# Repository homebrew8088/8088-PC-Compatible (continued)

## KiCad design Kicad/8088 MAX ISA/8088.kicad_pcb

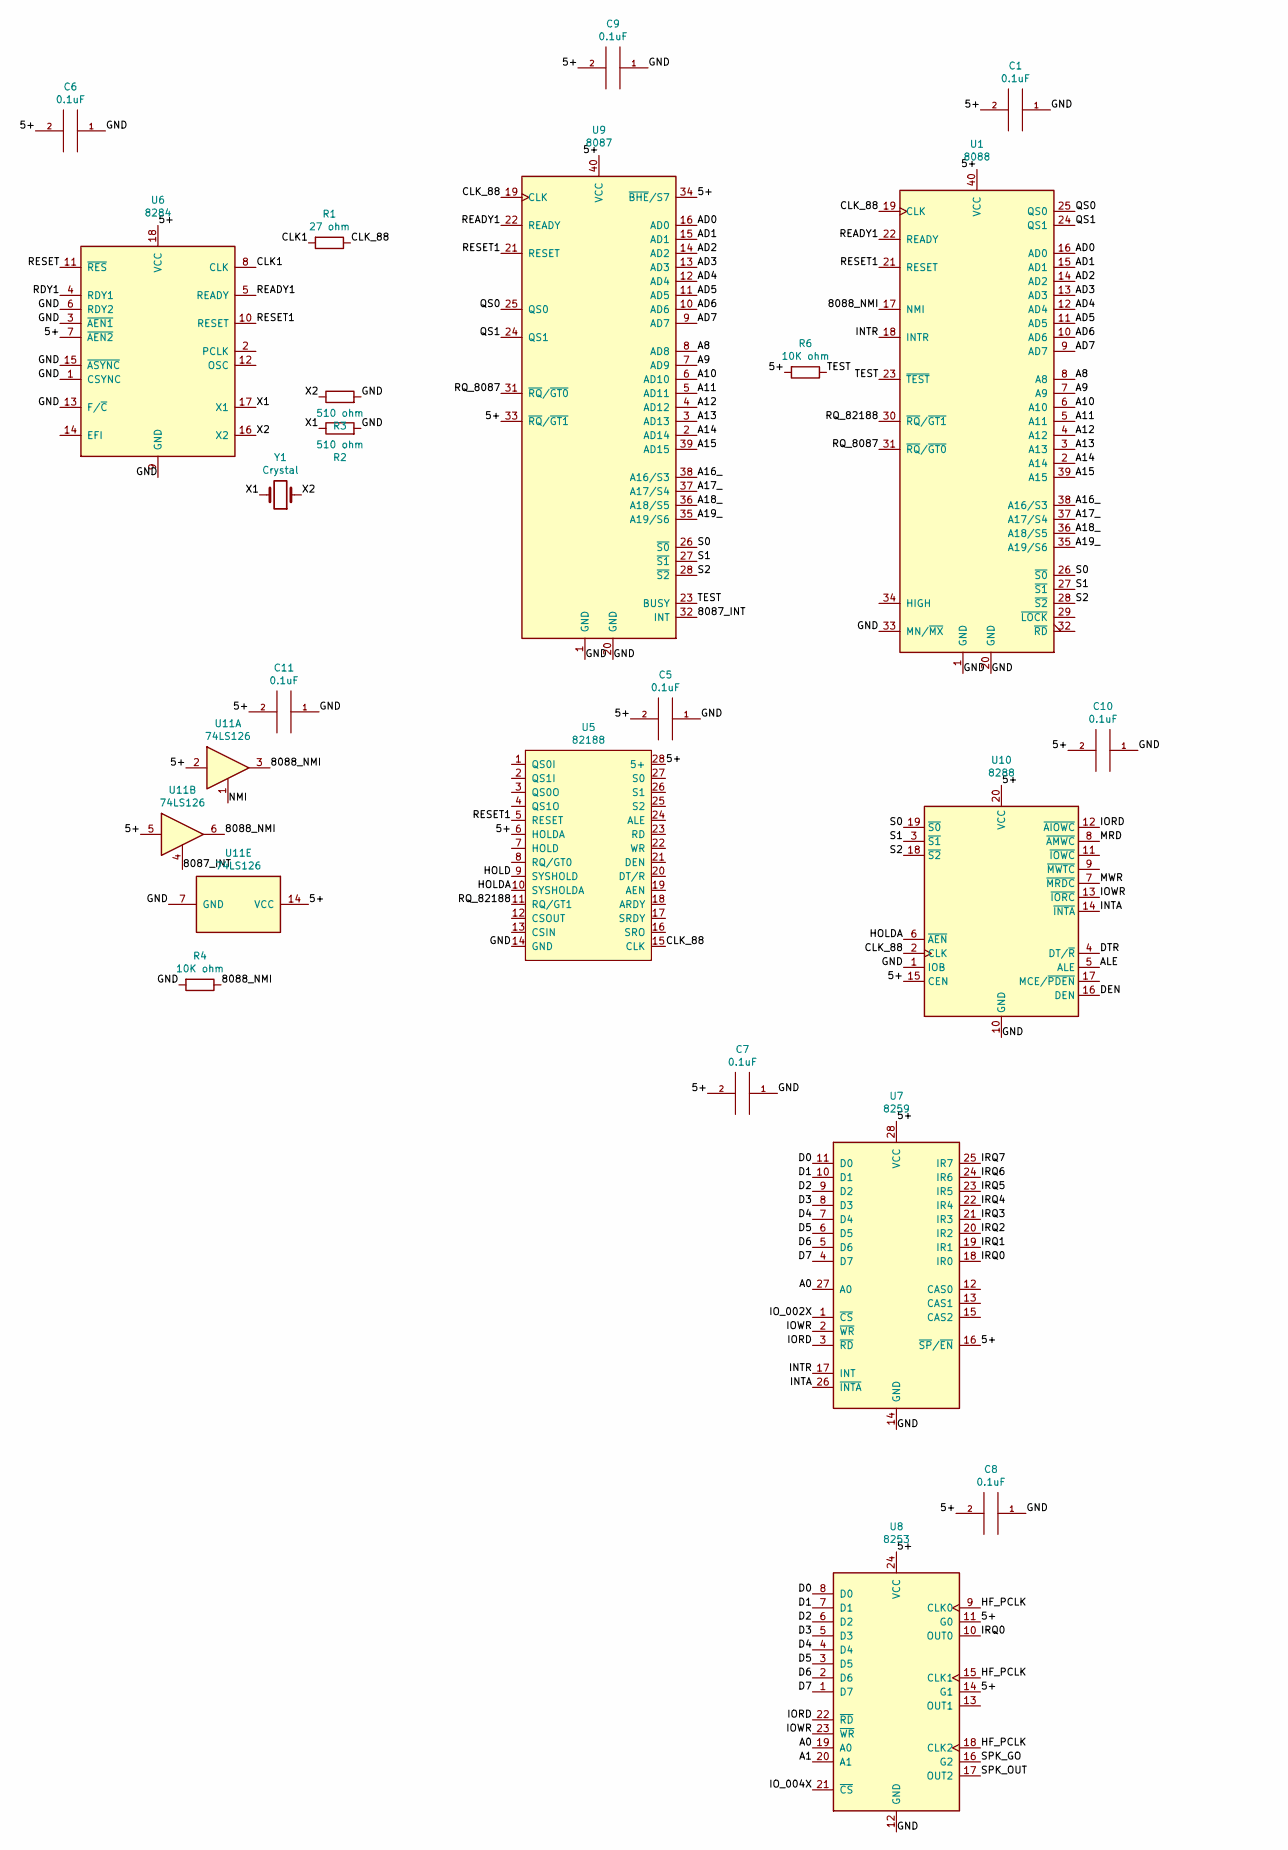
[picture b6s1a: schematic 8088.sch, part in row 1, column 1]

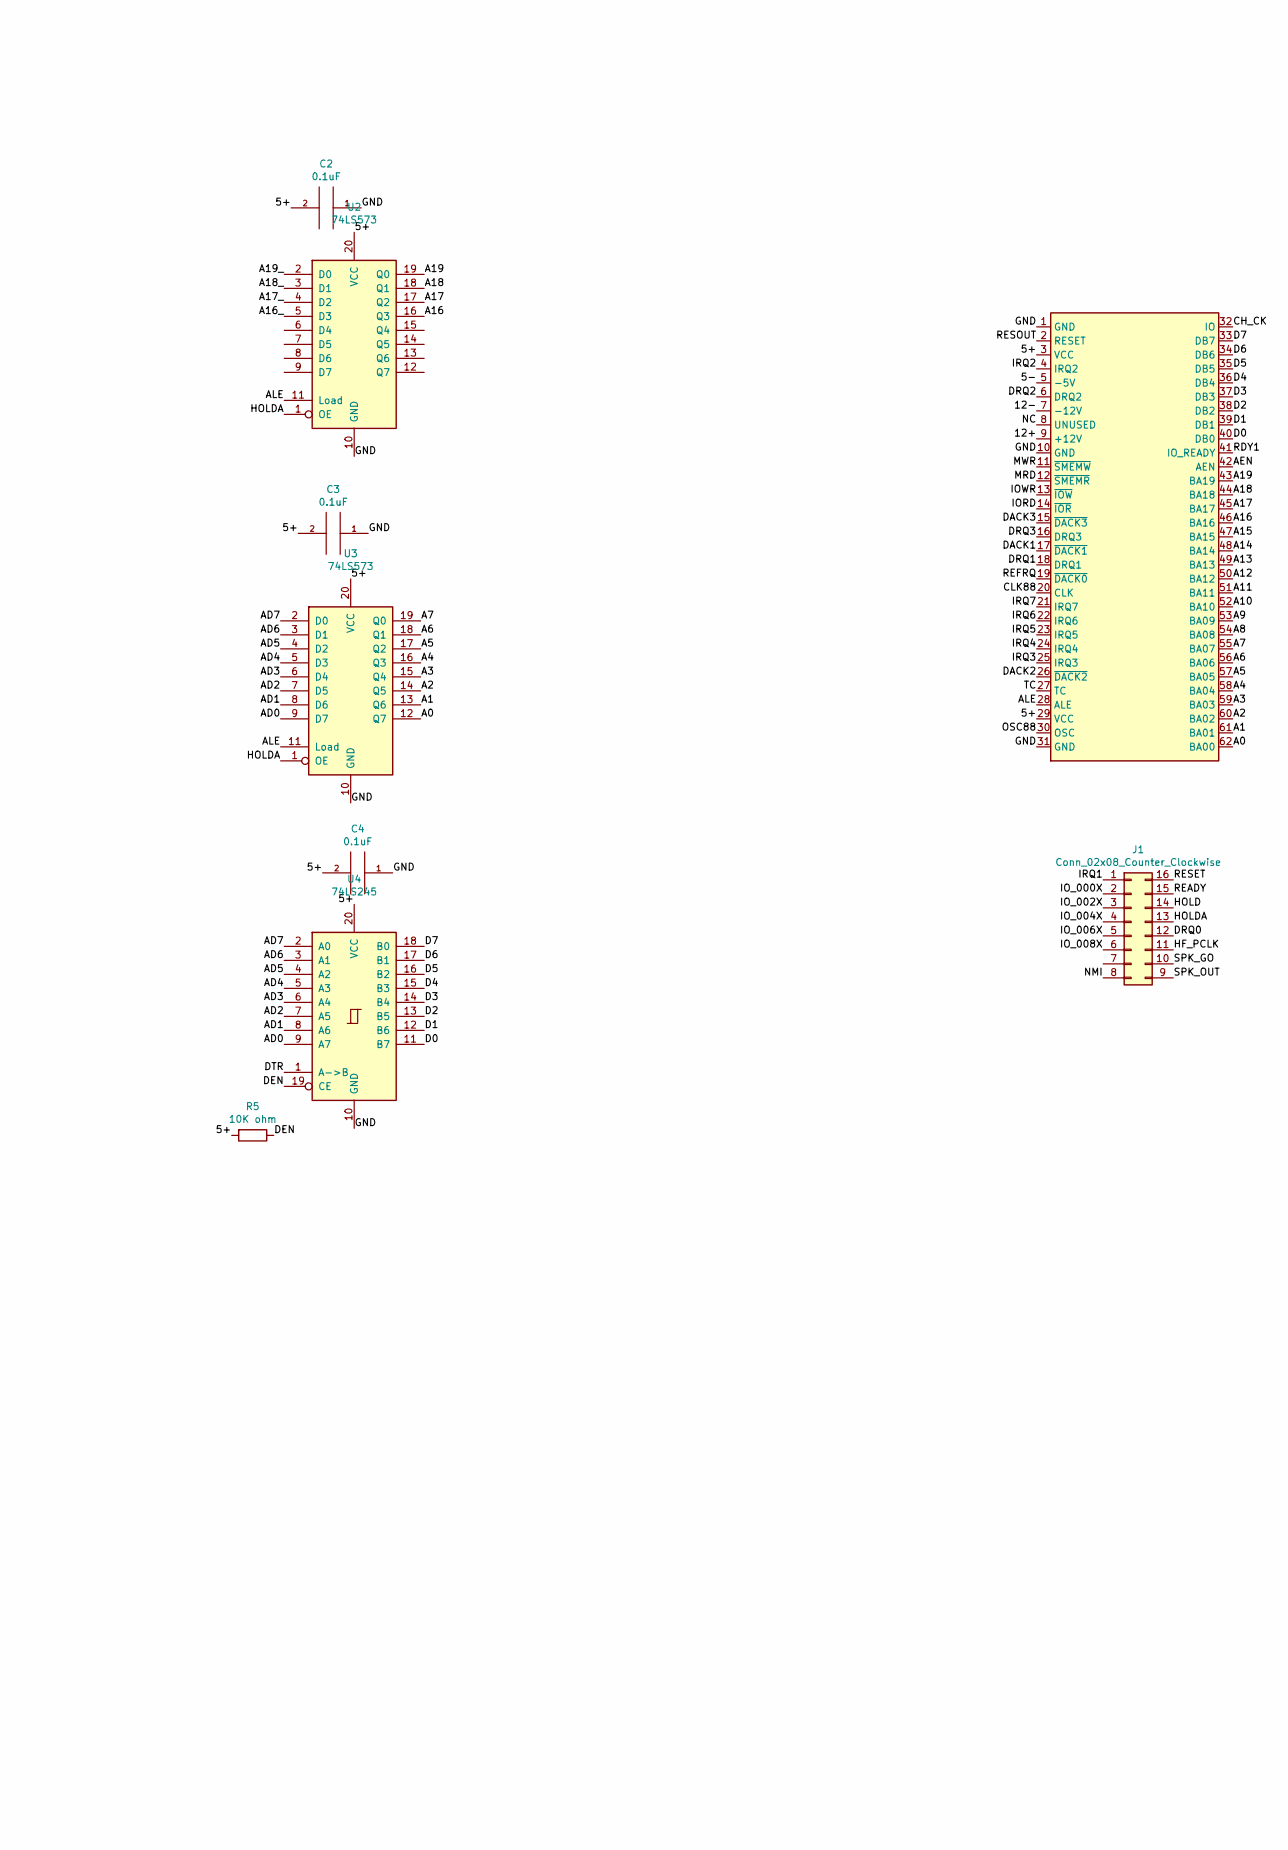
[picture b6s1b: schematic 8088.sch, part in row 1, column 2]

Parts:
C1, C2, C3, C4, C5, C6, C7, C8, C9, C10, C11: 0.1uF; C_Disc_D4.3mm_W1.9mm_P5.00mm
J1: Conn_02x08_Counter_Clockwise; 16_EDGE_CARD_BUS
J9: Bus_ISA_8bit; BUS_8_BIT
R1: 27 ohm; R_Axial_DIN0207_L6.3mm_D2.5mm_P10.16mm_Horizontal
R2, R3: 510 ohm; R_Axial_DIN0207_L6.3mm_D2.5mm_P10.16mm_Horizontal
R4, R5, R6: 10K ohm; R_Axial_DIN0207_L6.3mm_D2.5mm_P10.16mm_Horizontal
U1: 8088; DIP-40_W15.24mm
U2, U3: 74LS573; DIP-20_W7.62mm
U4: 74LS245; DIP-20_W7.62mm
U5: 82188; DIP-28_W15.24mm
U6: 8284; DIP-18_W7.62mm
U7: 8259; DIP-28_W15.24mm
U8: 8253; DIP-24_W15.24mm
U9: 8087; DIP-40_W15.24mm
U10: 8288; DIP-20_W7.62mm
U11: 74LS126; DIP-14_W7.62mm
Y1: Crystal; Crystal_HC18-U_Vertical

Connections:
/5+: C1.2, C2.2, C3.2, C4.2, C5.2, C6.2, C7.2, C8.2, C9.2, C10.2, C11.2, J9.3 (VCC), J9.29 (VCC), R5.2, R6.2, U1.40 (VCC), U2.20 (VCC), U3.20 (VCC), U4.20 (VCC), U5.6 (HOLDA), U5.28 (5+), U6.7 (~AEN2~), U6.18 (VCC), U7.16 (~SP~/~EN~), U7.28 (VCC), U8.11 (G0), U8.14 (G1), U8.24 (VCC), U9.33 (~RQ~/~GT1~), U9.34 (~BHE~/S7), U9.40 (VCC), U10.15 (CEN), U10.20 (VCC), U11.2, U11.5, U11.14 (VCC)
/5-: J9.5 (-5V)
/12+: J9.9 (+12V)
/12-: J9.7 (-12V)
/8087_INT: U9.32 (INT), U11.4
/8088_NMI: R4.1, U1.17 (NMI), U11.3, U11.6
/A0: J9.62 (BA00), U3.12 (Q7), U7.27 (A0), U8.19 (A0)
/A1: J9.61 (BA01), U3.13 (Q6), U8.20 (A1)
/A2: J9.60 (BA02), U3.14 (Q5)
/A3: J9.59 (BA03), U3.15 (Q4)
/A4: J9.58 (BA04), U3.16 (Q3)
/A5: J9.57 (BA05), U3.17 (Q2)
/A6: J9.56 (BA06), U3.18 (Q1)
/A7: J9.55 (BA07), U3.19 (Q0)
/A8: J9.54 (BA08), U1.8 (A8), U9.8 (AD8)
/A9: J9.53 (BA09), U1.7 (A9), U9.7 (AD9)
/A10: J9.52 (BA10), U1.6 (A10), U9.6 (AD10)
/A11: J9.51 (BA11), U1.5 (A11), U9.5 (AD11)
/A12: J9.50 (BA12), U1.4 (A12), U9.4 (AD12)
/A13: J9.49 (BA13), U1.3 (A13), U9.3 (AD13)
/A14: J9.48 (BA14), U1.2 (A14), U9.2 (AD14)
/A15: J9.47 (BA15), U1.39 (A15), U9.39 (AD15)
/A16: J9.46 (BA16), U2.16 (Q3)
/A16_: U1.38 (A16/S3), U2.5 (D3), U9.38 (A16/S3)
/A17: J9.45 (BA17), U2.17 (Q2)
/A17_: U1.37 (A17/S4), U2.4 (D2), U9.37 (A17/S4)
/A18: J9.44 (BA18), U2.18 (Q1)
/A18_: U1.36 (A18/S5), U2.3 (D1), U9.36 (A18/S5)
/A19: J9.43 (BA19), U2.19 (Q0)
/A19_: U1.35 (A19/S6), U2.2 (D0), U9.35 (A19/S6)
/AD0: U1.16 (AD0), U3.9 (D7), U4.9 (A7), U9.16 (AD0)
/AD1: U1.15 (AD1), U3.8 (D6), U4.8 (A6), U9.15 (AD1)
/AD2: U1.14 (AD2), U3.7 (D5), U4.7 (A5), U9.14 (AD2)
/AD3: U1.13 (AD3), U3.6 (D4), U4.6 (A4), U9.13 (AD3)
/AD4: U1.12 (AD4), U3.5 (D3), U4.5 (A3), U9.12 (AD4)
/AD5: U1.11 (AD5), U3.4 (D2), U4.4 (A2), U9.11 (AD5)
/AD6: U1.10 (AD6), U3.3 (D1), U4.3 (A1), U9.10 (AD6)
/AD7: U1.9 (AD7), U3.2 (D0), U4.2 (A0), U9.9 (AD7)
/AEN: J9.42 (AEN)
/ALE: J9.28 (ALE), U2.11 (Load), U3.11 (Load), U10.5 (ALE)
/CH_CK: J9.32 (IO)
/CLK1: R1.2, U6.8 (CLK)
/CLK88: J9.20 (CLK)
/CLK_88: R1.1, U1.19 (CLK), U5.15 (CLK), U9.19 (CLK), U10.2 (CLK)
/D0: J9.40 (DB0), U4.11 (B7), U7.11 (D0), U8.8 (D0)
/D1: J9.39 (DB1), U4.12 (B6), U7.10 (D1), U8.7 (D1)
/D2: J9.38 (DB2), U4.13 (B5), U7.9 (D2), U8.6 (D2)
/D3: J9.37 (DB3), U4.14 (B4), U7.8 (D3), U8.5 (D3)
/D4: J9.36 (DB4), U4.15 (B3), U7.7 (D4), U8.4 (D4)
/D5: J9.35 (DB5), U4.16 (B2), U7.6 (D5), U8.3 (D5)
/D6: J9.34 (DB6), U4.17 (B1), U7.5 (D6), U8.2 (D6)
/D7: J9.33 (DB7), U4.18 (B0), U7.4 (D7), U8.1 (D7)
/DACK1: J9.17 (~DACK1)
/DACK2: J9.26 (~DACK2)
/DACK3: J9.15 (~DACK3)
/DEN: R5.1, U4.19 (CE), U10.16 (DEN)
/DRQ0: J1.12
/DRQ1: J9.18 (DRQ1)
/DRQ2: J9.6 (DRQ2)
/DRQ3: J9.16 (DRQ3)
/DTR: U4.1 (A->B), U10.4 (DT/~R~)
/GND: C1.1, C2.1, C3.1, C4.1, C5.1, C6.1, C7.1, C8.1, C9.1, C10.1, C11.1, J9.1 (GND), J9.10 (GND), J9.31 (GND), R2.2, R3.2, R4.2, U1.1 (GND), U1.20 (GND), U1.33 (MN/~MX~), U2.10 (GND), U3.10 (GND), U4.10 (GND), U5.14 (GND), U6.1 (CSYNC), U6.3 (~AEN1~), U6.6 (RDY2), U6.9 (GND), U6.13 (F/~C~), U6.15 (~ASYNC~), U7.14 (GND), U8.12 (GND), U9.1 (GND), U9.20 (GND), U10.1 (IOB), U10.10 (GND), U11.7 (GND); also elsewhere on the board
/HF_PCLK: J1.11, U8.9 (CLK0), U8.15 (CLK1), U8.18 (CLK2)
/HOLD: J1.14, U5.9 (SYSHOLD)
/HOLDA: J1.13, U2.1 (OE), U3.1 (OE), U5.10 (SYSHOLDA), U10.6 (~AEN~)
/INTA: U7.26 (~INTA~), U10.14 (~INTA~)
/INTR: U1.18 (INTR), U7.17 (INT)
/IORD: J9.14 (~IOR), U7.3 (~RD~), U8.22 (~RD~), U10.12 (~AIOWC~)
/IOWR: J9.13 (~IOW), U7.2 (~WR~), U8.23 (~WR~), U10.13 (~IORC~)
/IO_000X: J1.2
/IO_002X: J1.3, U7.1 (~CS~)
/IO_004X: J1.4, U8.21 (~CS~)
/IO_006X: J1.5
/IO_008X: J1.6
/IRQ0: U7.18 (IR0), U8.10 (OUT0)
/IRQ1: J1.1, U7.19 (IR1)
/IRQ2: J9.4 (IRQ2), U7.20 (IR2)
/IRQ3: J9.25 (IRQ3), U7.21 (IR3)
/IRQ4: J9.24 (IRQ4), U7.22 (IR4)
/IRQ5: J9.23 (IRQ5), U7.23 (IR5)
/IRQ6: J9.22 (IRQ6), U7.24 (IR6)
/IRQ7: J9.21 (IRQ7), U7.25 (IR7)
/MRD: J9.12 (~SMEMR), U10.8 (~AMWC~)
/MWR: J9.11 (~SMEMW), U10.7 (~MRDC~)
/NC: J9.8 (UNUSED)
/NMI: J1.8, U11.1
/OSC88: J9.30 (OSC)
/QS0: U1.25 (QS0), U9.25 (QS0)
/QS1: U1.24 (QS1), U9.24 (QS1)
/RDY1: J9.41 (IO_READY), U6.4 (RDY1)
/READY: J1.15
/READY1: U1.22 (READY), U6.5 (READY), U9.22 (READY)
/REFRQ: J9.19 (~DACK0)
/RESET: J1.16, U6.11 (~RES~)
/RESET1: U1.21 (RESET), U5.5 (RESET), U6.10 (RESET), U9.21 (RESET)
/RESOUT: J9.2 (RESET)
/RQ_8087: U1.31 (~RQ~/~GT0~), U9.31 (~RQ~/~GT0~)
/RQ_82188: U1.30 (~RQ~/~GT1~), U5.11 (RQ/GT1)
/S0: U1.26 (~S0~), U9.26 (~S0~), U10.19 (~S0~)
/S1: U1.27 (~S1~), U9.27 (~S1~), U10.3 (~S1~)
/S2: U1.28 (~S2~), U9.28 (~S2~), U10.18 (~S2~)
/SPK_GO: J1.10, U8.16 (G2)
/SPK_OUT: J1.9, U8.17 (OUT2)
/TC: J9.27 (TC)
/TEST: R6.1, U1.23 (~TEST~), U9.23 (BUSY)
/X1: R2.1, U6.17 (X1), Y1.2
/X2: R3.1, U6.16 (X2), Y1.1

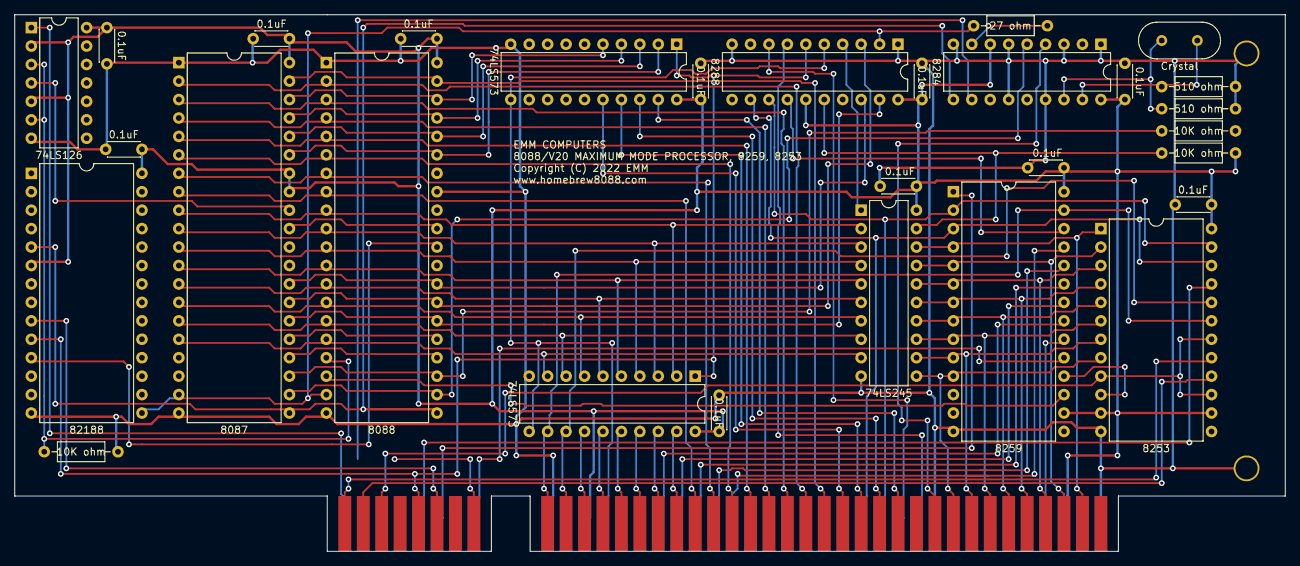
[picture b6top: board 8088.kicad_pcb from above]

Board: 2 copper layers, 175.0 x 73.9 mm, 33 parts (0 on the bottom side), 85 nets.

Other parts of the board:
R: L; Large_Via
R#2: L; Large_Via

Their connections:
/GND: R.1, R#2.1; also elsewhere on the board
